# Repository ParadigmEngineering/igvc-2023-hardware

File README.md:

# igvc-2023-hardware
Intelligent Ground Vehicle Competition (Spring 2023) hardware for the Paradigm Engineering Student Group

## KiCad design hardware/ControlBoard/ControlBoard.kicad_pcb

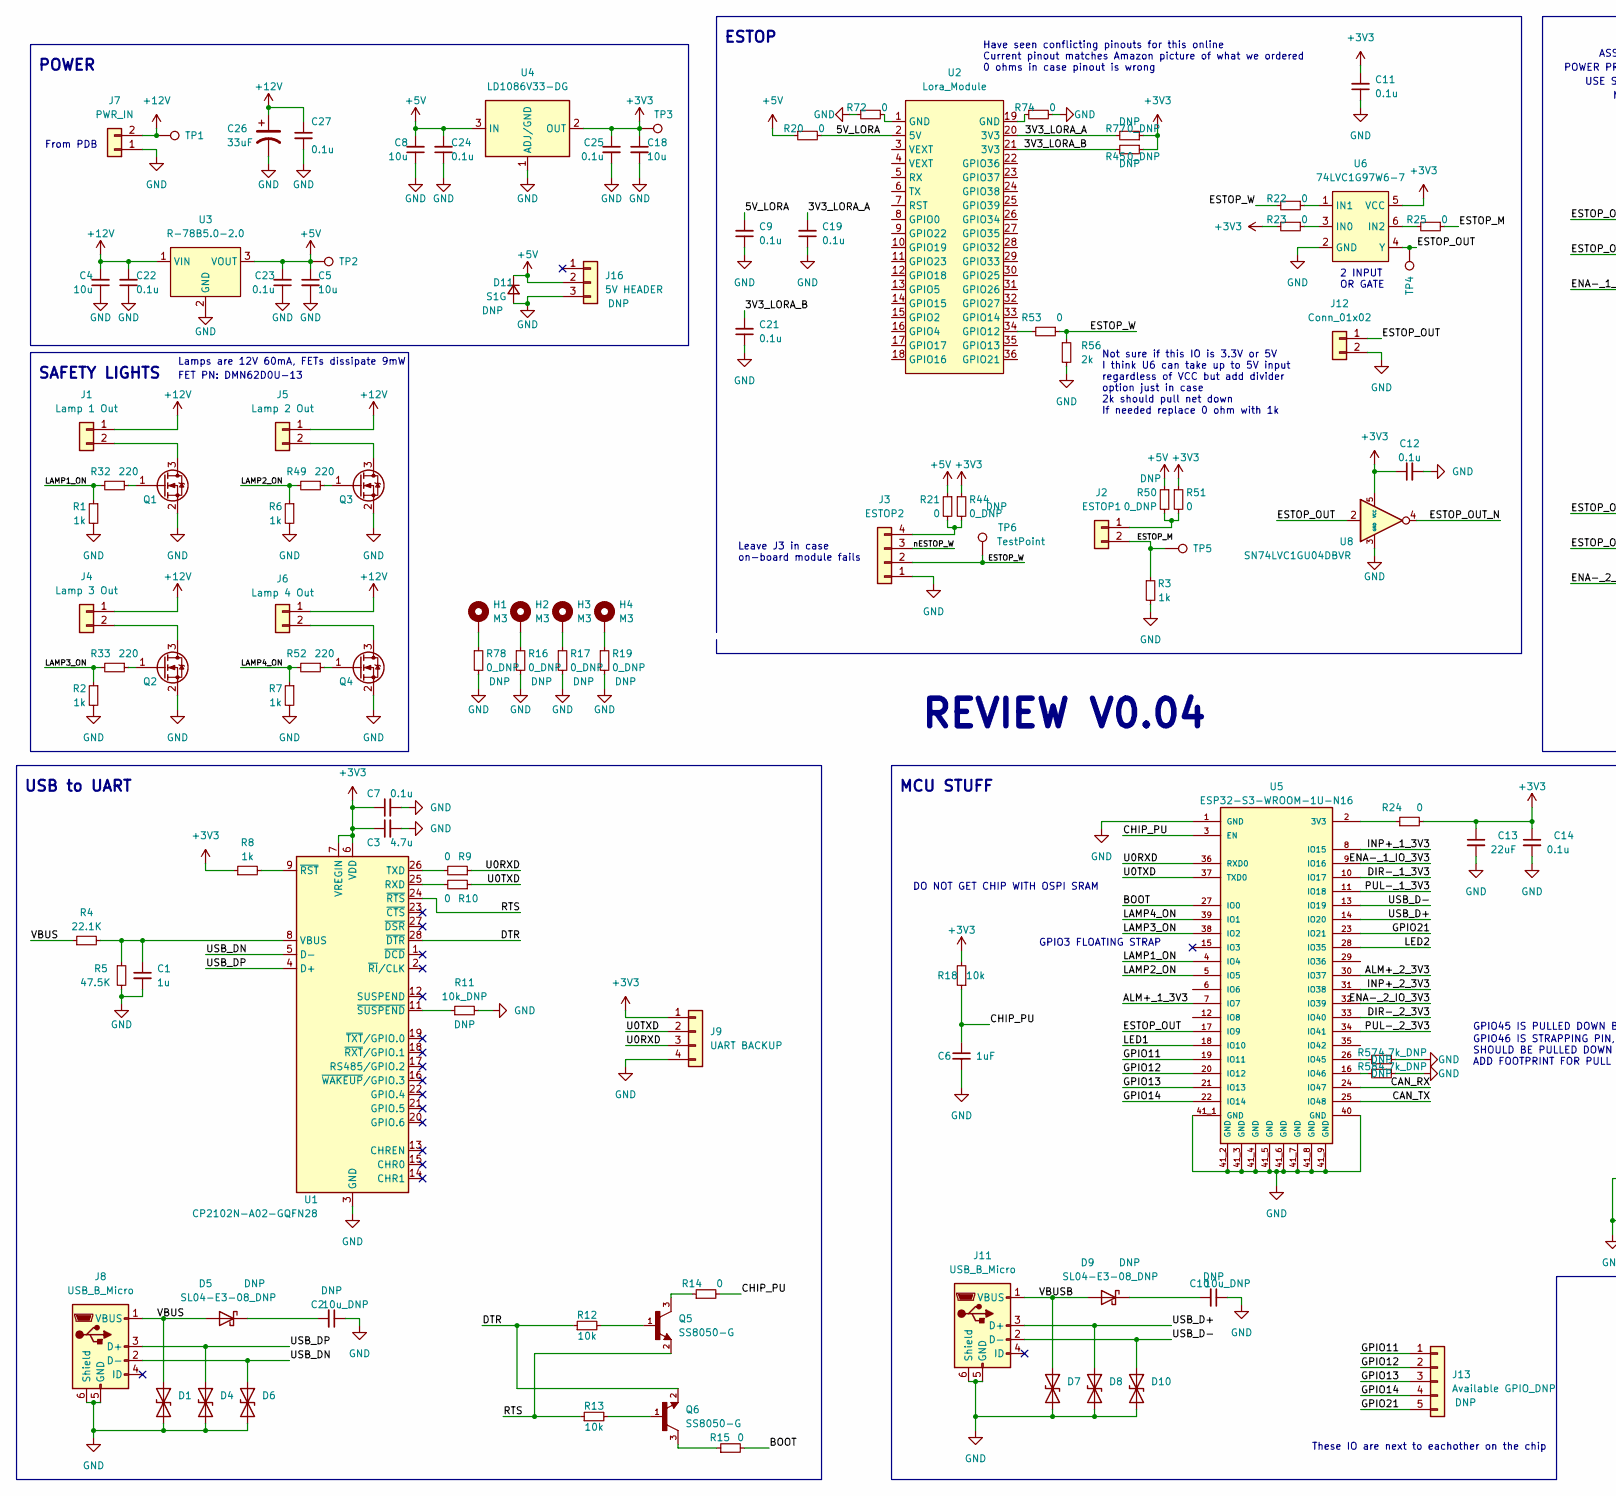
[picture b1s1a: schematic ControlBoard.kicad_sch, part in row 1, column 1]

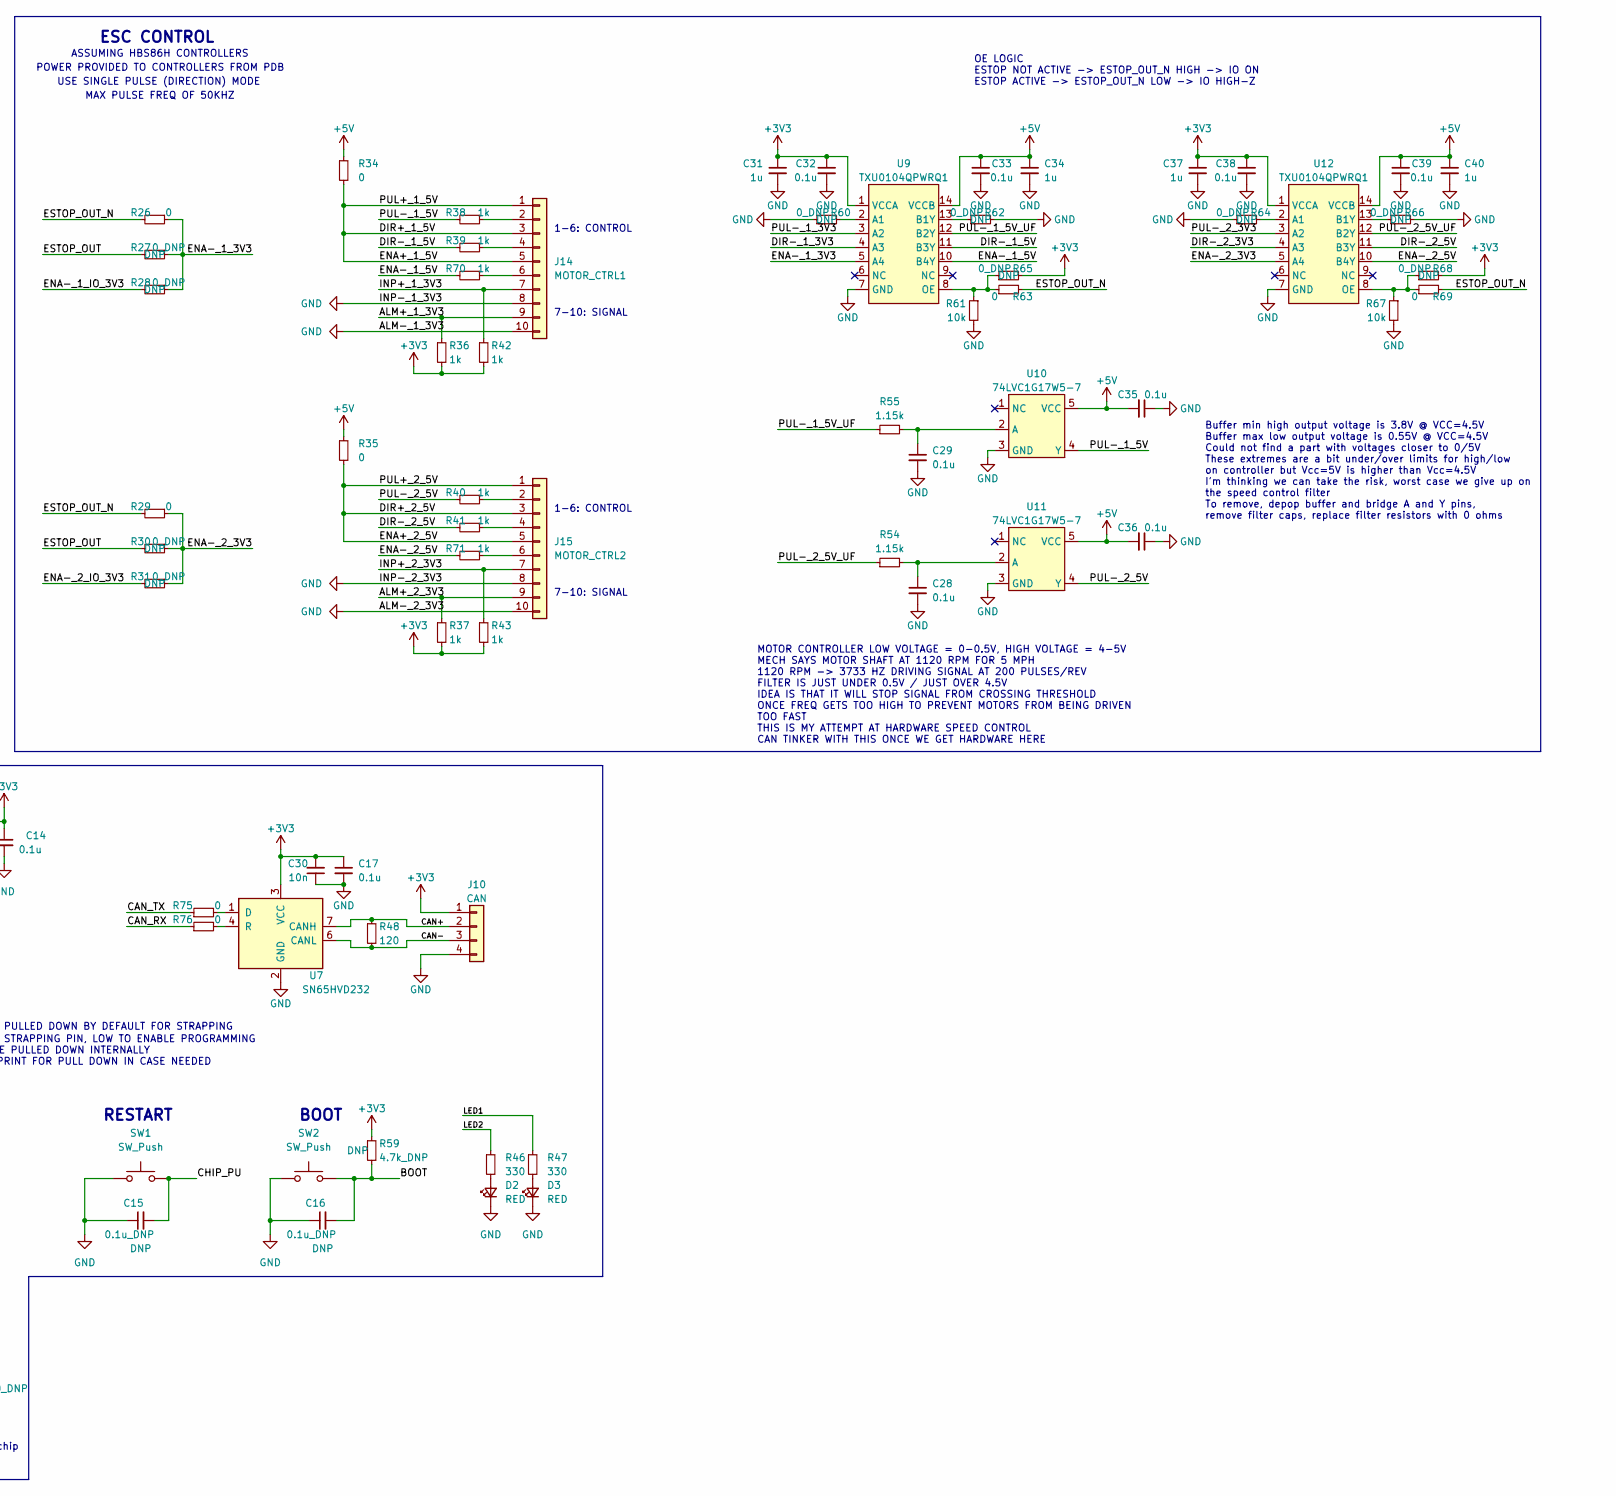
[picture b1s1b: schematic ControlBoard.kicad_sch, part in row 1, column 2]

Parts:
C1: 1u; C_0805_2012Metric; LCSC C116352
C2, C10: 10u_DNP; C_0805_2012Metric; Voltage 5V
C3: 4.7u; C_0805_2012Metric; LCSC C87998
C4: 10u; C_0805_2012Metric; Voltage 12V; LCSC C237493
C5, C8: 10u; C_0805_2012Metric; Voltage 5V; LCSC C237493
C6: 1uF; C_0805_2012Metric; Rating 16V; Voltage 3.3V; LCSC C116352
C7, C9, C12, C19, C21: 0.1u; C_0805_2012Metric; LCSC C519981
C11, C17, C25, C32, C38: 0.1u; C_0805_2012Metric; Voltage 3.3V; LCSC C519981
C13: 22uF; C_0805_2012Metric; Rating 25V; LCSC C128856
C14: 0.1u; C_0805_2012Metric; Rating 25V; LCSC C519981
C15, C16: 0.1u_DNP; C_0805_2012Metric; Voltage 3.3V
C18: 10u; C_0805_2012Metric; Voltage 3.3V; LCSC C237493
C22, C27: 0.1u; C_0805_2012Metric; Voltage 12V; LCSC C519981
C23, C24, C28, C29, C33, C35, C36, C39: 0.1u; C_0805_2012Metric; Voltage 5V; LCSC C519981
C26: 33uF; CP_Radial_D8.0mm_P3.50mm; Digikey 1189-2152-ND
C30: 10n; C_0805_2012Metric; Voltage 3.3V; LCSC C2688117
C31, C37: 1u; C_0805_2012Metric; Voltage 3.3V; LCSC C116352
C34, C40: 1u; C_0805_2012Metric; Voltage 5V; LCSC C116352
D1, D4, D6, D7, D8, D10: SMAJ5.0CA; D_SMA; Digikey SMAJ5.0CALFCT-ND
D2, D3: RED; LED_0603_1608Metric; Digikey 160-1445-1-ND
D5, D9: SL04-E3-08_DNP; D_SMF; Digikey SL04-E3-08GICT-ND
D11: S1G; D_SMA; Digikey 1655-S1GCT-ND
H1, H2, H3, H4: M3; MountingHole_3.2mm_M3_Pad_Via
J1: Lamp 1 Out; Molex_Micro-Fit_3.0_43650-0200_1x02_P3.00mm_Horizontal; Digikey WM1860-ND
J2: ESTOP1; Molex_Micro-Fit_3.0_43650-0200_1x02_P3.00mm_Horizontal; Digikey WM1860-ND
J3: ESTOP2; JST_PH_B4B-PH-K_1x04_P2.00mm_Vertical; LCSC C566011
J4: Lamp 3 Out; Molex_Micro-Fit_3.0_43650-0200_1x02_P3.00mm_Horizontal; Digikey WM1860-ND
J5: Lamp 2 Out; Molex_Micro-Fit_3.0_43650-0200_1x02_P3.00mm_Horizontal; Digikey WM1860-ND
J6: Lamp 4 Out; Molex_Micro-Fit_3.0_43650-0200_1x02_P3.00mm_Horizontal; Digikey WM1860-ND
J7: PWR_IN; Molex_Micro-Fit_3.0_43650-0200_1x02_P3.00mm_Horizontal; Digikey WM1860-ND
J8, J11: USB_B_Micro; USB_Micro-B_Amphenol_10118194_Horizontal; Digikey 609-4618-1-ND
J9: UART BACKUP; PinHeader_1x04_P2.54mm_Vertical; Digikey 664-G800W304018EU-ND
J10: CAN; JST_PH_B4B-PH-K_1x04_P2.00mm_Vertical; LCSC C566011
J12: Conn_01x02; Molex_Micro-Fit_3.0_43650-0200_1x02_P3.00mm_Horizontal; Digikey WM1860-ND
J13: Available GPIO_DNP; PinHeader_1x05_P1.27mm_Vertical; Digikey 2057-HPH1-A-05-UA-ND
J14: MOTOR_CTRL1; Molex_Micro-Fit_3.0_43650-1000_1x10_P3.00mm_Horizontal; Digikey 23-0436501000-ND
J15: MOTOR_CTRL2; Molex_Micro-Fit_3.0_43650-1000_1x10_P3.00mm_Horizontal; Digikey 23-0436501000-ND
J16: 5V HEADER; Molex_KK-254_AE-6410-03A_1x03_P2.54mm_Vertical; Digikey WM4112-ND
Q1, Q2, Q3, Q4: DMN62D0U-13; Digikey DMN62D0U-13DICT-ND
Q5, Q6: SS8050-G; TRANS_SS8050-G; PARTREV A; Digikey 641-1790-1-ND
R1, R2, R3, R6, R7, R8, R36, R37, R38, R39, R40, R41, R42, R43, R70, R71: 1k; R_0805_2012Metric; LCSC C510097
R4: 22.1K; R_0805_2012Metric; LCSC C273840
R5: 47.5K; R_0805_2012Metric; LCSC C137519
R9, R10, R14, R15, R20, R21, R22, R23, R25, R26, R29, R34, R35, R51, R53, R63, R69, R72, R74, R75, R76: 0; R_0805_2012Metric; LCSC C237773
R11: 10k_DNP; R_0805_2012Metric
R12, R13, R18, R61, R67: 10k; R_0805_2012Metric; LCSC C110775
R16, R17, R19, R78: 0_DNP; R_0805_2012Metric
R24: 0; R_0805_2012Metric; LCSC C96345
R27, R28, R30, R31, R44, R45, R50, R60, R62, R64, R65, R66, R68, R77: 0_DNP; R_0805_2012Metric; LCSC C237773
R32, R33, R49, R52: 220; R_0805_2012Metric; LCSC C114519
R46, R47: 330; R_0805_2012Metric; LCSC C105878
R48: 120; R_0805_2012Metric; Digikey 311-120CRCT-ND
R54, R55: 1.15k; R_0805_2012Metric; LCSC C309566
R56: 2k; R_0805_2012Metric; LCSC C127985
R57, R58, R59: 4.7k_DNP; R_0805_2012Metric
SW1, SW2: SW_Push; SW_SPST_B3U-1100P-B; Digikey SW1104CT-ND
TP1, TP2, TP3, TP4, TP5, TP6: TestPoint; TestPoint_Pad_D1.0mm
U1: CP2102N-A02-GQFN28; QFN-28-1EP_5x5mm_P0.5mm_EP3.35x3.35mm; LCSC C964632
U2: Lora_Module
U3: R-78B5.0-2.0; Digikey 945-3042-ND
U4: LD1086V33-DG; TO-220-3_Vertical; Digikey 497-17820-ND
U5: ESP32-S3-WROOM-1U-N16; XCVR_ESP32-S3-WROOM-1U; PARTREV v0.6; LCSC C2980298
U6: 74LVC1G97W6-7; Digikey 74LVC1G97W6-7CT-ND
U7: SN65HVD232; SOIC-8_3.9x4.9mm_P1.27mm; LCSC C30530
U8: SN74LVC1GU04DBVR; SOT-23-5; LCSC C81934
U9, U12: TXU0104QPWRQ1; Digikey 296-TXU0104QPWRQ1CT-ND
U10, U11: 74LVC1G17W5-7; Digikey 74LVC1G17W5-7CT-ND

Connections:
+3V3: C3.1, C7.1, C11.2, C12.1, C13.1, C14.1, C17.1, C18.1, C25.1, C30.2, C31.1, C32.1, C37.1, C38.1, J9.1, J10.1, R8.1, R18.2, R23.2, R24.2, R36.2, R37.2, R42.2, R43.2, R44.1, R45.1, R51.1, R59.1, R65.2, R68.2, R77.1, TP3.1, U1.6 (VDD), U1.7 (VREGIN), U4.2 (OUT), U6.5 (VCC), U7.3 (VCC), U8.5 (VCC), U9.1 (VCCA), U12.1 (VCCA)
+5V: C5.1, C8.2, C23.2, C24.2, C33.1, C34.1, C35.2, C36.2, C39.1, C40.1, D11.1 (K), J16.2, R20.1, R21.1, R34.1, R35.1, R50.1, TP2.1, U3.3 (VOUT), U4.3 (IN), U9.14 (VCCB), U10.5 (VCC), U11.5 (VCC), U12.14 (VCCB)
+12V: C4.2, C22.2, C26.1, C27.1, J1.1, J4.1, J5.1, J6.1, J7.2, TP1.1, U3.1 (VIN)
/3V3_LORA_A: C19.2, R77.2, U2.20 (3V3)
/3V3_LORA_B: C21.2, R45.2, U2.21 (3V3)
/5V_LORA: C9.2, R20.2, U2.2 (5V)
/ALM+_1_3V3: J14.9, R36.1, U5.7 (IO7)
/ALM+_2_3V3: J15.9, R37.1, U5.30 (IO37)
/BOOT: C16.2, R15.2, R59.2, SW2.2, U5.27 (IO0)
/CAN+: J10.2, R48.1, U7.7 (CANH)
/CAN-: J10.3, R48.2, U7.6 (CANL)
/CAN_RX: R76.1, U5.24 (IO47)
/CAN_TX: R75.1, U5.25 (IO48)
/CHIP_PU: C6.1, C15.2, R14.2, R18.1, SW1.2, U5.3 (EN)
/DIR+_1_5V: J14.1, J14.3, J14.5, R34.2
/DIR+_2_5V: J15.1, J15.3, J15.5, R35.2
/DIR-_1_3V3: U5.10 (IO17), U9.4 (A3)
/DIR-_1_5V: R39.2, U9.11 (B3Y)
/DIR-_2_3V3: U5.33 (IO40), U12.4 (A3)
/DIR-_2_5V: R41.2, U12.11 (B3Y)
/DTR: Q6.2, R12.1, U1.28 (~DTR)
/ENA-_1_3V3: R26.1, R27.1, R28.1, U9.5 (A4)
/ENA-_1_5V: R70.2, U9.10 (B4Y)
/ENA-_1_IO_3V3: R28.2, U5.9 (IO16)
/ENA-_2_3V3: R29.1, R30.1, R31.1, U12.5 (A4)
/ENA-_2_5V: R71.2, U12.10 (B4Y)
/ENA-_2_IO_3V3: R31.2, U5.32 (IO39)
/ESTOP_M: J2.2, R3.1, R25.1, TP5.1
/ESTOP_OUT: J12.1, R27.2, R30.2, TP4.1, U5.17 (IO9), U6.4 (Y), U8.2
/ESTOP_OUT_N: R26.2, R29.2, R63.2, R69.2, U8.4
/ESTOP_W: J3.2, R22.2, R53.1, R56.1, TP6.1
/GPIO11: J13.1, U5.19 (IO11)
/GPIO12: J13.2, U5.20 (IO12)
/GPIO13: J13.3, U5.21 (IO13)
/GPIO14: J13.4, U5.22 (IO14)
/GPIO21: J13.5, U5.23 (IO21)
/INP+_1_3V3: J14.7, R42.1, U5.8 (IO15)
/INP+_2_3V3: J15.7, R43.1, U5.31 (IO38)
/LAMP1_ON: R1.1, R32.2, U5.4 (IO4)
/LAMP2_ON: R6.1, R49.2, U5.5 (IO5)
/LAMP3_ON: R2.1, R33.2, U5.38 (IO2)
/LAMP4_ON: R7.1, R52.2, U5.39 (IO1)
/LED1: R47.1, U5.18 (IO10)
/LED2: R46.1, U5.28 (IO35)
/PUL-_1_3V3: U5.11 (IO18), U9.3 (A2)
/PUL-_1_5V: R38.2, U10.4 (Y)
/PUL-_1_5V_UF: R55.1, U9.12 (B2Y)
/PUL-_2_3V3: U5.34 (IO41), U12.3 (A2)
/PUL-_2_5V: R40.2, U11.4 (Y)
/PUL-_2_5V_UF: R54.1, U12.12 (B2Y)
/RTS: Q5.2, R13.1, U1.24 (~RTS)
/U0RXD: J9.3, R9.1, U5.36 (RXD0)
/U0TXD: J9.2, R10.1, U5.37 (TXD0)
/USB_D+: D8.1 (A1), J11.3 (D+), U5.14 (IO20)
/USB_D-: D10.1 (A1), J11.2 (D-), U5.13 (IO19)
/USB_DN: D6.1 (A1), J8.2 (D-), U1.5 (D-)
/USB_DP: D4.1 (A1), J8.3 (D+), U1.4 (D+)
/VBUS: D1.1 (A1), D5.2 (A), J8.1 (VBUS), R4.1
/VBUSB: D7.1 (A1), D9.2 (A), J11.1 (VBUS)
/nESTOP_W: J3.3
GND: C1.2, C2.1, C3.2, C4.1, C5.2, C6.2, C7.2, C8.1, C9.1, C10.1, C11.1, C12.2, C13.2, C14.2, C15.1, C16.1, C17.2, C18.2, C19.1, C21.1, C22.1, C23.1, C24.1, C25.2, C26.2, C27.2, C28.2, C29.2, C30.1, C31.2, C32.2, C33.2, C34.2, C35.1, C36.1, C37.2, C38.2, C39.2, C40.2, D1.2 (A2), D2.1 (K), D3.1 (K), D4.2 (A2), D6.2 (A2), D7.2 (A2), D8.2 (A2), D10.2 (A2), D11.2 (A), J3.1, J7.1, J8.5 (GND), J8.6 (Shield), J9.4, J10.4, J11.5 (GND), J11.6 (Shield), J12.2, J14.8, J14.10, J15.8, J15.10, J16.3, Q1.2 (S), Q2.2 (S), Q3.2 (S), Q4.2 (S), R1.2, R2.2, R3.2, R5.2, R6.2, R7.2, R11.2, R16.2, R17.2, R19.2, R56.2, R57.1, R58.1, R60.1, R61.2, R62.2, R64.1, R66.2, R67.2, R72.1, R74.2, R78.2, SW1.1, SW2.1, U1.3 (GND), U1.29 (GND), U3.2 (GND), U4.1 (ADJ/GND), U5.1 (GND), U5.40 (GND), U5.41_1 (GND), U5.41_2 (GND), U5.41_3 (GND), U5.41_4 (GND), U5.41_5 (GND), U5.41_6 (GND), U5.41_7 (GND), U5.41_8 (GND), U5.41_9 (GND), U6.2 (GND), U7.2 (GND), U8.3 (GND), U9.7 (GND), U10.3 (GND), U11.3 (GND), U12.7 (GND)
unnamed: C1.1, R4.2, R5.1, U1.8 (VBUS)
unnamed: C2.2, D5.1 (K)
unnamed: C10.2, D9.1 (K)
unnamed: C28.1, R54.2, U11.2 (A)
unnamed: C29.1, R55.2, U10.2 (A)
unnamed: D2.2 (A), R46.2
unnamed: D3.2 (A), R47.2
unnamed: H1.1, R78.1
unnamed: H2.1, R16.1
unnamed: H3.1, R17.1
unnamed: H4.1, R19.1
unnamed: J1.2, Q1.3 (D)
unnamed: J2.1, R50.2, R51.2
unnamed: J3.4, R21.2, R44.2
unnamed: J4.2, Q2.3 (D)
unnamed: J5.2, Q3.3 (D)
unnamed: J6.2, Q4.3 (D)
unnamed: J14.2, R38.1
unnamed: J14.4, R39.1
unnamed: J14.6, R70.1
unnamed: J15.2, R40.1
unnamed: J15.4, R41.1
unnamed: J15.6, R71.1
unnamed: Q1.1 (G), R32.1
unnamed: Q2.1 (G), R33.1
unnamed: Q3.1 (G), R49.1
unnamed: Q4.1 (G), R52.1
unnamed: Q5.1, R12.2
unnamed: Q5.3, R14.1
unnamed: Q6.1, R13.2
unnamed: Q6.3, R15.1
unnamed: R8.2, U1.9 (~RST)
unnamed: R9.2, U1.26 (TXD)
unnamed: R10.2, U1.25 (RXD)
unnamed: R11.1, U1.11 (~SUSPEND)
unnamed: R22.1, U6.1 (IN1)
unnamed: R23.1, U6.3 (IN0)
unnamed: R24.1, U5.2 (3V3)
unnamed: R25.2, U6.6 (IN2)
unnamed: R53.2, U2.34 (GPIO12)
unnamed: R57.2, U5.26 (IO45)
unnamed: R58.2, U5.16 (IO46)
unnamed: R60.2, U9.2 (A1)
unnamed: R61.1, R63.1, R65.1, U9.8 (OE)
unnamed: R62.1, U9.13 (B1Y)
unnamed: R64.2, U12.2 (A1)
unnamed: R66.1, U12.13 (B1Y)
unnamed: R67.1, R68.1, R69.1, U12.8 (OE)
unnamed: R72.2, U2.1 (GND)
unnamed: R74.1, U2.19 (GND)
unnamed: R75.2, U7.1 (D)
unnamed: R76.2, U7.4 (R)

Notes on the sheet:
2 INPUT OR GATE
These IO are next to eachother on the chip
Not sure if this IO is 3.3V or 5V I think U6 can take up to 5V input regardless of VCC but add divider option just in case 2k should pull net down If needed replace 0 ohm with 1k
FET PN: DMN62D0U-13
Have seen conflicting pinouts for this online Current pinout matches Amazon picture of what we ordered 0 ohms in case pinout is wrong
POWER
ASSUMING HBS86H CONTROLLERS
MCU STUFF
SAFETY LIGHTS
Buffer min high output voltage is 3.8V @ VCC=4.5V Buffer max low output voltage is 0.55V @ VCC=4.5V Could not find a part with voltages closer to 0/5V These extremes are a bit under/over limits for high/low on controller but Vcc=5V is higher than Vcc=4.5V I'm thinking we can take the risk, worst ca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
1-6: CONTROL
POWER PROVIDED TO CONTROLLERS FROM PDB
ESC CONTROL
GPIO3 FLOATING STRAP
MOTOR CONTROLLER LOW VOLTAGE = 0-0.5V, HIGH VOLTAGE = 4-5V MECH SAYS MOTOR SHAFT AT 1120 RPM FOR 5 MPH 1120 RPM -> 3733 HZ DRIVING SIGNAL AT 200 PULSES/REV FILTER IS JUST UNDER 0.5V / JUST OVER 4.5V IDEA IS THAT IT WILL STOP SIGNAL FROM CROSSING THRESHOLD ONCE FREQ GETS TOO HIGH TO PREVENT MOTORS F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
REVIEW V0.04
USB to UART
From PDB
7-10: SIGNAL
Leave J3 in case on-board module fails
USE SINGLE PULSE (DIRECTION) MODE
GPIO46 IS STRAPPING PIN, LOW TO ENABLE PROGRAMMING SHOULD BE PULLED DOWN INTERNALLY ADD FOOTPRINT FOR PULL DOWN IN CASE NEEDED
DO NOT GET CHIP WITH OSPI SRAM
RESTART
ESTOP
BOOT
Lamps are 12V 60mA, FETs dissipate 9mW
GPIO45 IS PULLED DOWN BY DEFAULT FOR STRAPPING
MAX PULSE FREQ OF 50KHZ
OE LOGIC ESTOP NOT ACTIVE -> ESTOP_OUT_N HIGH -> IO ON ESTOP ACTIVE -> ESTOP_OUT_N LOW -> IO HIGH-Z

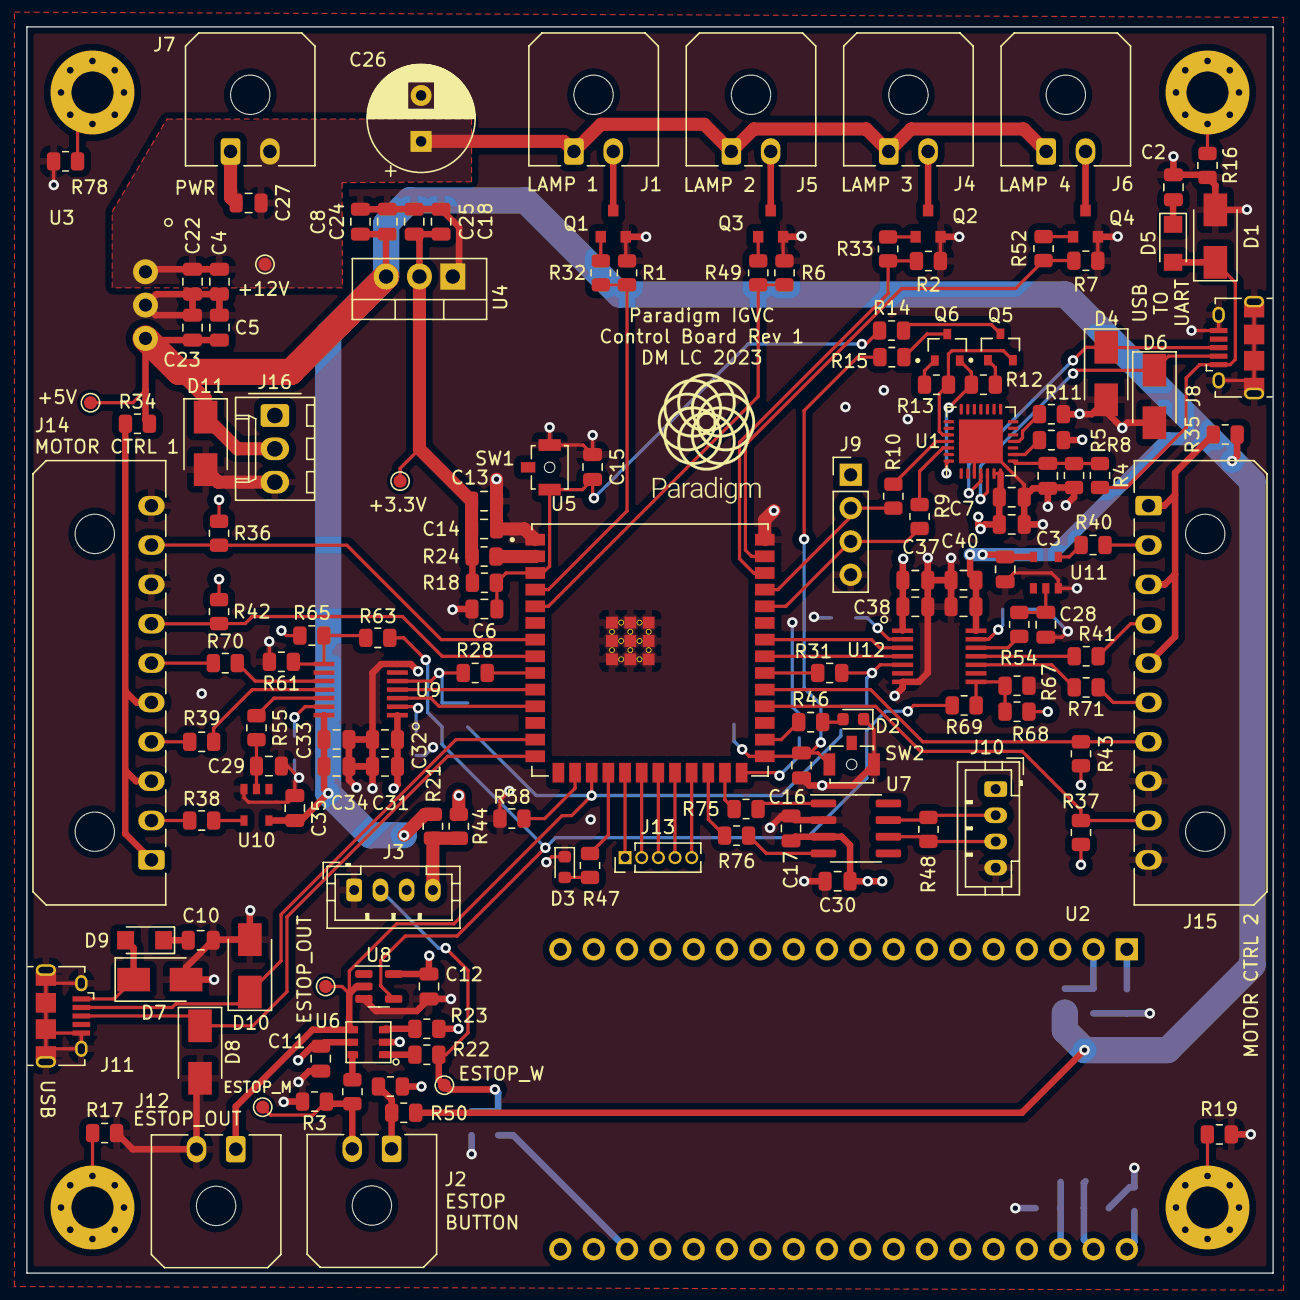
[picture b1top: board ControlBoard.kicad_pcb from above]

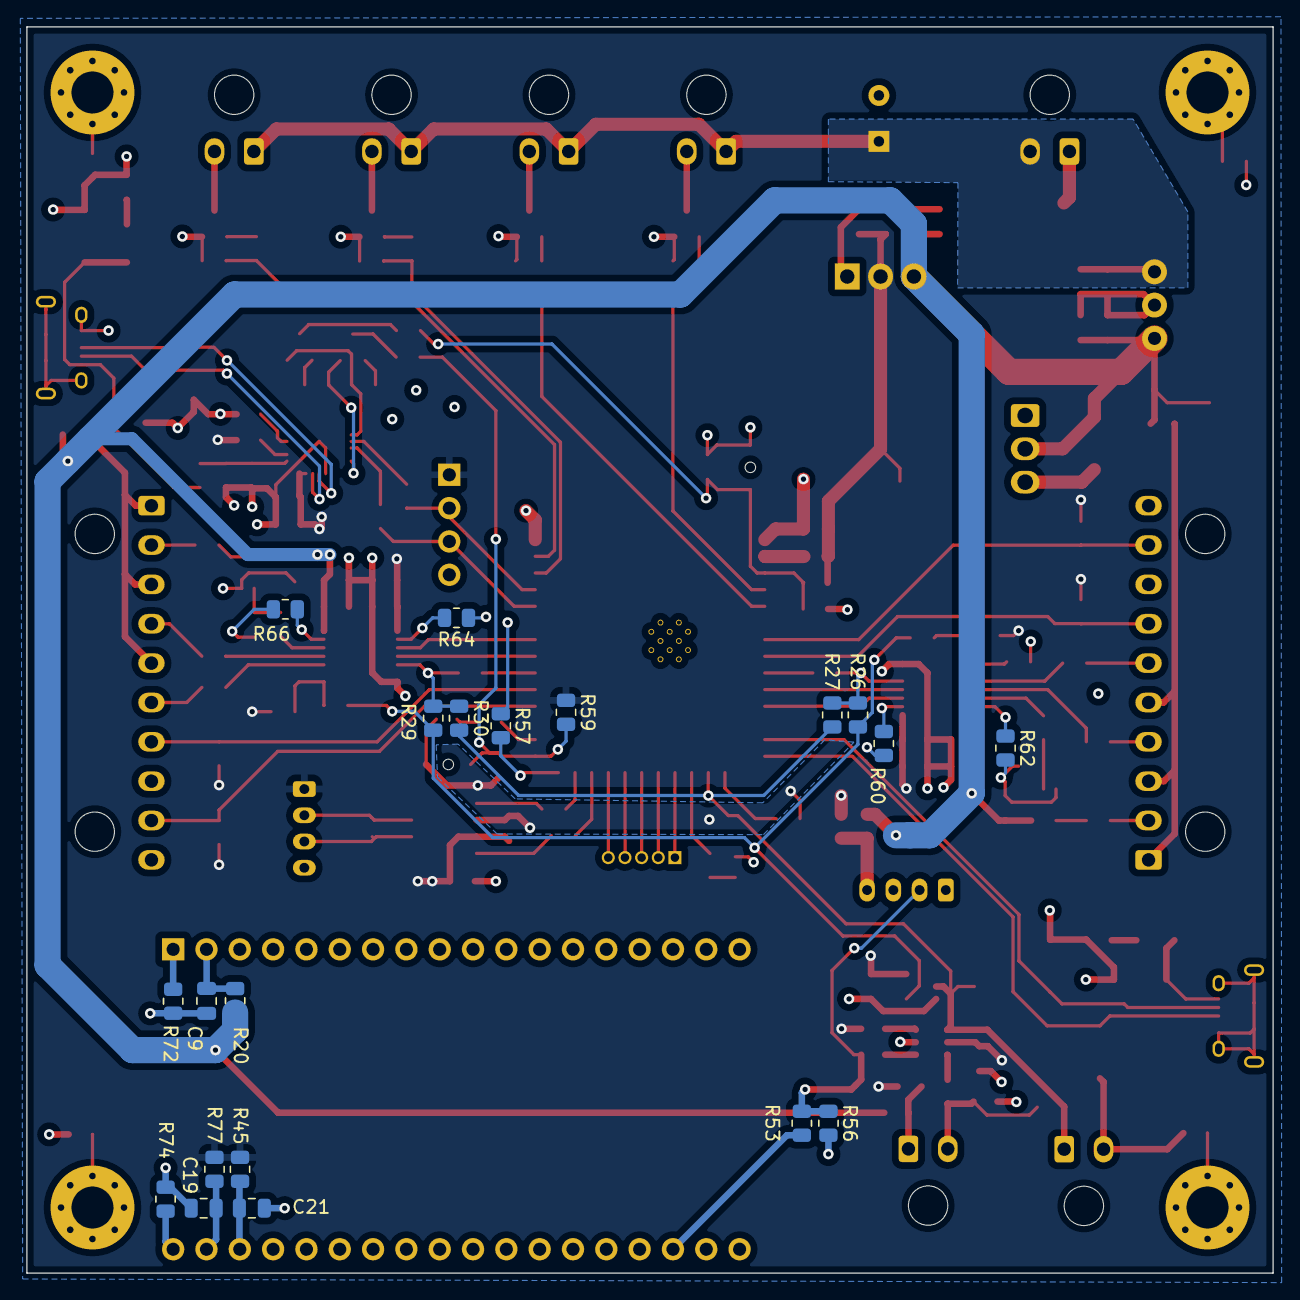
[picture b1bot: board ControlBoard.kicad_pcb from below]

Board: 4 copper layers, 95.0 x 95.0 mm, 173 parts (20 on the bottom side), 112 nets.

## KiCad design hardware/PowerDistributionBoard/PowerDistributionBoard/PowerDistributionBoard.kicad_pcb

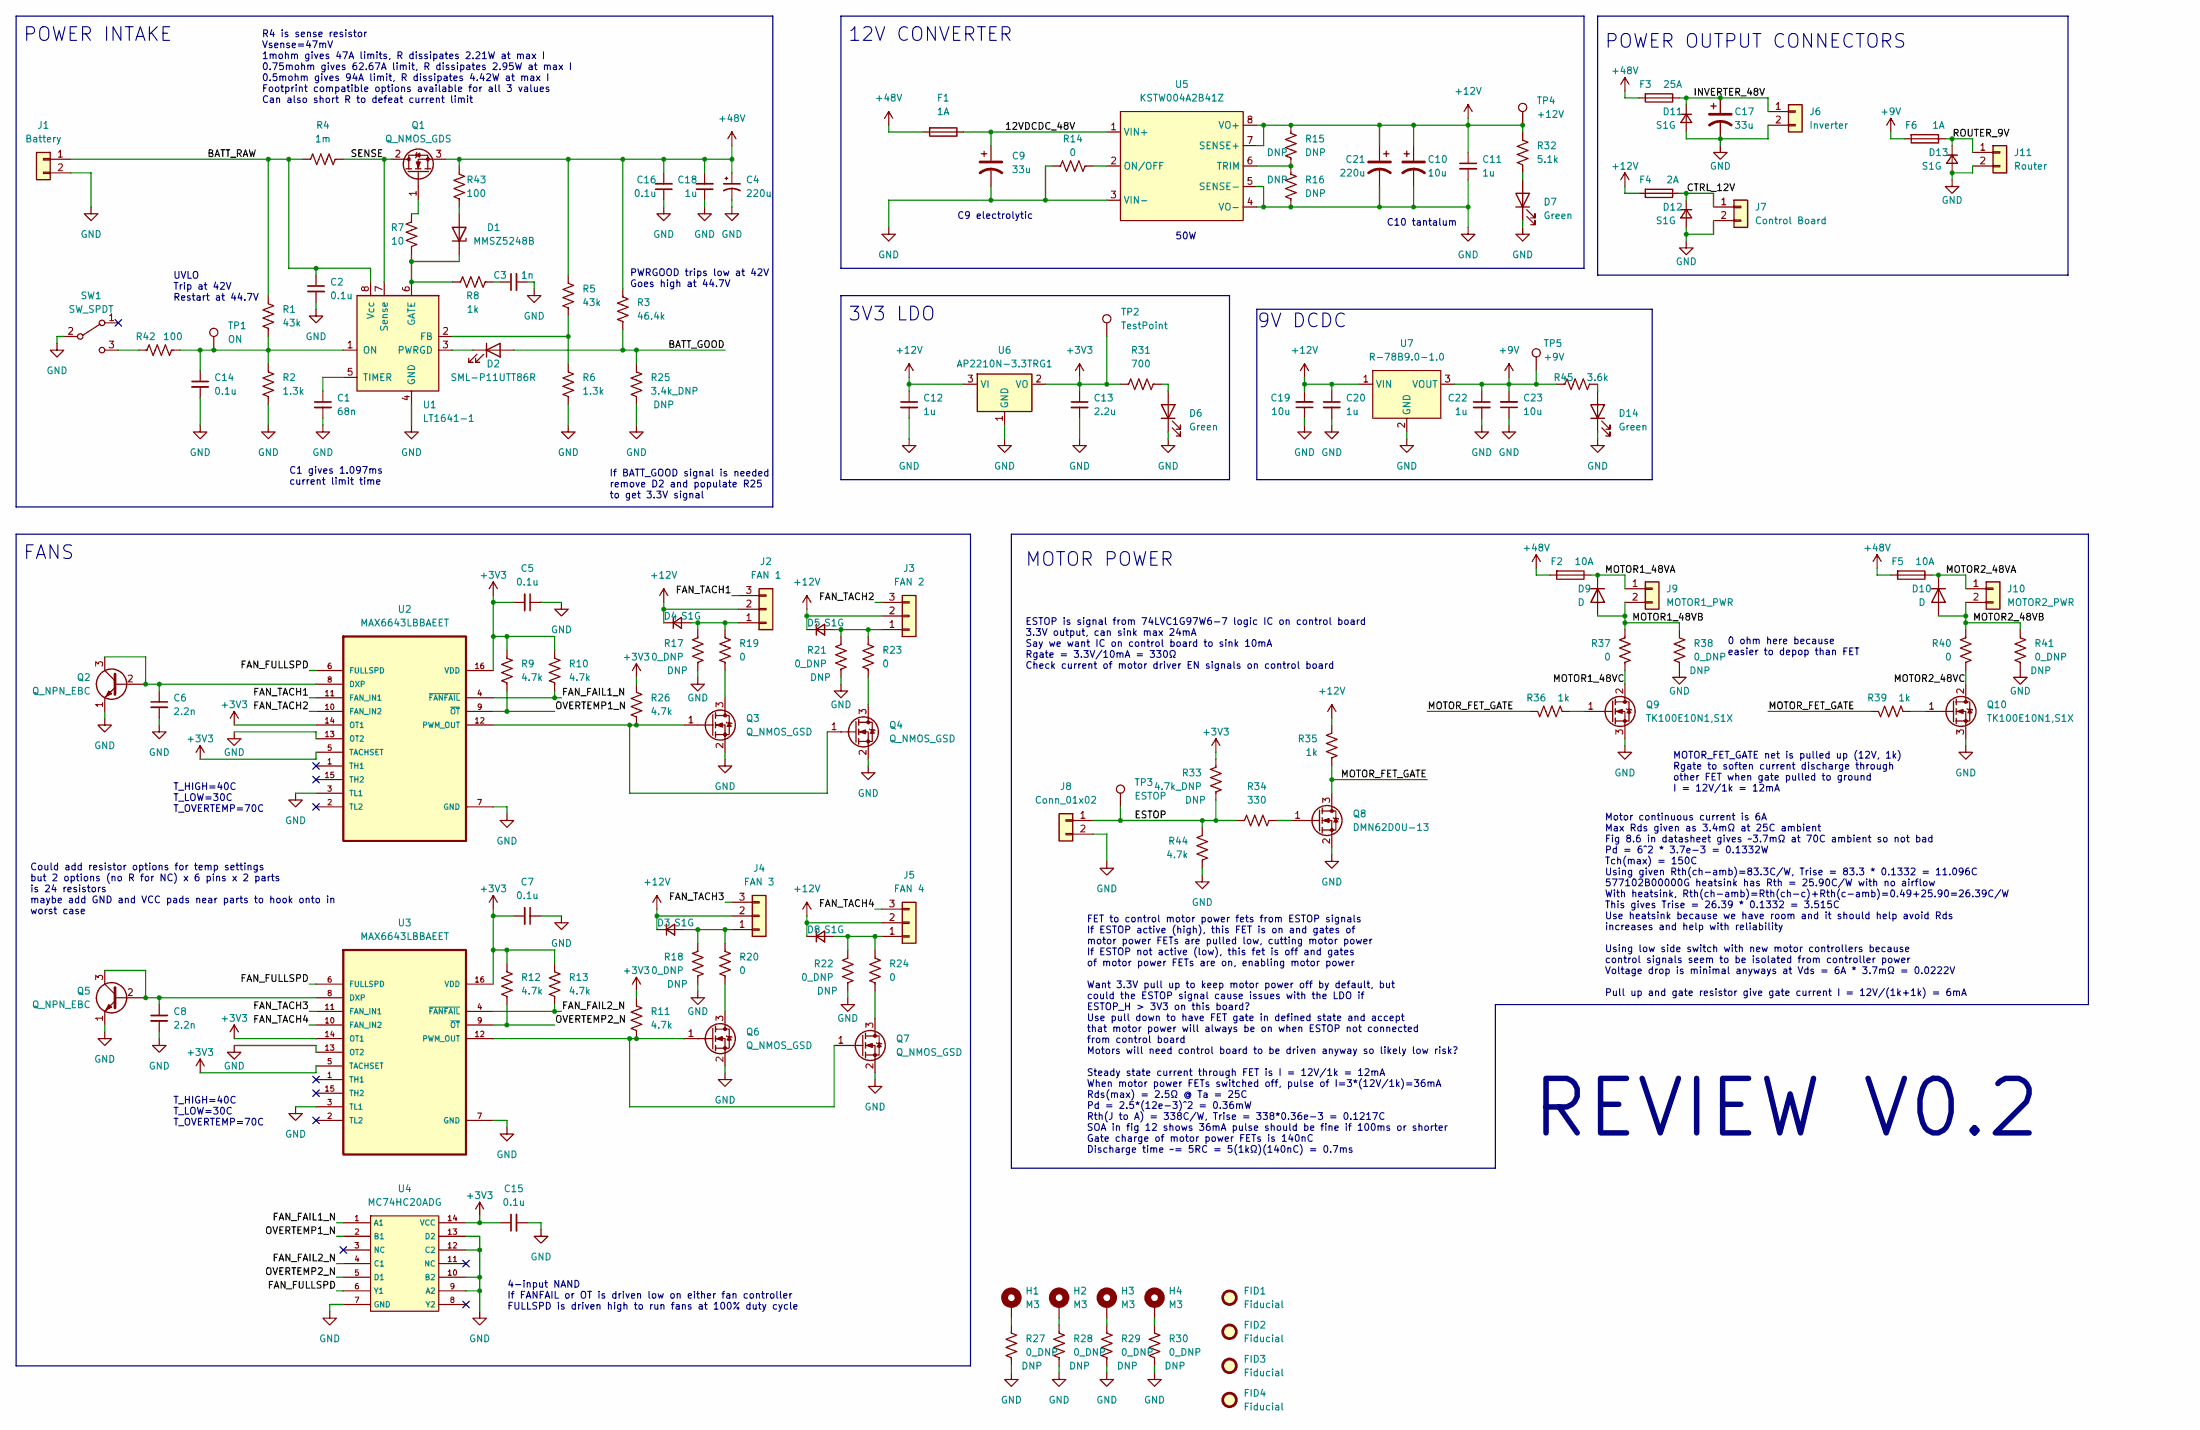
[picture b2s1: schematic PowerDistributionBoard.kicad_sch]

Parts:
C1: 68n; C_0805_2012Metric; Voltage 44V; LCSC C113842
C2, C14, C16: 0.1u; C_0805_2012Metric; Voltage 48V; LCSC C28233
C3: 1n; C_0805_2012Metric; Voltage 68V; LCSC C16005
C4: 220u; CP_Radial_D16.0mm_P7.50mm; Voltage 48V; Digikey 493-5867-ND
C5, C7, C15: 0.1u; C_0805_2012Metric; Voltage 3.3V; LCSC C597440
C6, C8: 2.2n; C_0805_2012Metric; Voltage 0.8V; LCSC C1728
C9, C17: 33u; CP_Radial_D10.0mm_P5.00mm; Digikey 1189-2207-ND
C10: 10u; C_1206_3216Metric; Digikey 478-10001-1-ND
C11, C12, C20: 1u; C_0805_2012Metric; Voltage 12V; LCSC C116352
C13: 2.2u; C_0805_2012Metric; Voltage 3.3V; LCSC C107366
C18: 1u; C_0805_2012Metric; Voltage 48V; LCSC C28233
C19: 10u; C_0805_2012Metric; Voltage 12V; LCSC C237493
C21: 220u; CP_Radial_D6.3mm_P2.50mm; Voltage 12V; Digikey 1189-2913-ND
C22: 1u; C_0805_2012Metric; Voltage 9V; LCSC C116352
C23: 10u; C_0805_2012Metric; Voltage 9V; LCSC C237493
D1: MMSZ5248B; D_SOD-123; Digikey MMSZ5248B-HE3-08GICT-ND
D2: SML-P11UTT86R; LED_0402_1005Metric; Digikey SML-P11UTT86RCT-ND
D3, D4, D5, D8, D11, D12, D13: S1G; D_SMA; Digikey 1655-S1GCT-ND
D6, D7, D14: Green; LED_0805_2012Metric_Pad1.15x1.40mm_HandSolder; Digikey 492-2525-1-ND
D9, D10: D; VS-15AWL06FNTR-M3; Digikey VS-15AWL06FNTR-M3GICT-ND
F1, F6: 1A; 3557-2; Digikey 36-3557-2-ND
F2, F5: 10A; 3557-2; Digikey 36-3557-2-ND
F3: 25A; 3557-2; Digikey 36-3557-2-ND
F4: 2A; 3557-2; Digikey 36-3557-2-ND
FID1, FID2, FID3, FID4: Fiducial; Fiducial_1mm_Mask2mm
H1, H2, H3, H4: M3; MountingHole_3.2mm_M3_Pad_Via
J1: Battery; Molex_Mini-Fit_Sr_42820-22XX_1x02_P10.00mm_Horizontal; Digikey WM11250-ND
J2: FAN 1; Molex_KK-254_AE-6410-03A_1x03_P2.54mm_Vertical; Digikey WM4112-ND
J3: FAN 2; Molex_KK-254_AE-6410-03A_1x03_P2.54mm_Vertical; Digikey WM4112-ND
J4: FAN 3; Molex_KK-254_AE-6410-03A_1x03_P2.54mm_Vertical; Digikey WM4112-ND
J5: FAN 4; Molex_KK-254_AE-6410-03A_1x03_P2.54mm_Vertical; Digikey WM4112-ND
J6: Inverter; Molex_Mini-Fit_Sr_42820-22XX_1x02_P10.00mm_Horizontal; Digikey WM11250-ND
J7: Control Board; Molex_Micro-Fit_3.0_43650-0215_1x02_P3.00mm_Vertical; Digikey WM1917-ND
J8: Conn_01x02; Molex_Micro-Fit_3.0_43650-0215_1x02_P3.00mm_Vertical; Digikey WM1917-ND
J9: MOTOR1_PWR; Molex_Mini-Fit_Sr_42820-22XX_1x02_P10.00mm_Horizontal; Digikey WM11250-ND
J10: MOTOR2_PWR; Molex_Mini-Fit_Sr_42820-22XX_1x02_P10.00mm_Horizontal; Digikey WM11250-ND
J11: Router; Molex_Micro-Fit_3.0_43650-0215_1x02_P3.00mm_Vertical; Digikey WM1917-ND
Q1: Q_NMOS_GDS; TO-263-2; Digikey 296-49604-1-ND
Q2, Q5: Q_NPN_EBC; SST3904T116CT-ND; Digikey SST3904T116CT-ND
Q3, Q4, Q6, Q7: Q_NMOS_GSD; SC-59; Digikey BSR802NL6327HTSA1CT-ND
Q8: DMN62D0U-13; Digikey DMN62D0U-13DICT-ND
Q9, Q10: TK100E10N1,S1X; TO-220-3_Vertical; Digikey TK100E10N1S1X-ND
R1, R5: 43k; R_0805_2012Metric; LCSC C137524
R2, R6: 1.3k; R_0805_2012Metric; LCSC C137582
R3: 46.4k; R_0805_2012Metric; LCSC C317450
R4: 1m; Y14860R00075F9R; Digikey_0.75m 804-Y14860R00075F9RCT-ND
R7: 10; R_0805_2012Metric; LCSC C2074472
R8, R35, R36, R39: 1k; R_0805_2012Metric; LCSC C510097
R9, R10, R11, R12, R13, R26, R44: 4.7k; R_0805_2012Metric; LCSC C140869
R14, R19, R20, R23, R24: 0; R_0805_2012Metric; LCSC C237773
R15, R16: DNP; R_0805_2012Metric
R17, R18, R21, R22, R27, R28, R29, R30: 0_DNP; R_0805_2012Metric
R25: 3.4k_DNP; R_0805_2012Metric
R31: 700; R_0805_2012Metric; LCSC C483228
R32: 5.1k; R_0805_2012Metric; LCSC C84375
R33: 4.7k_DNP; R_0805_2012Metric
R34: 330; R_0805_2012Metric; LCSC C105878
R37, R40: 0; R_2512_6332Metric; Digikey HCJ2512ZT0R00CT-ND
R38, R41: 0_DNP; R_2512_6332Metric; Digikey HCJ2512ZT0R00CT-ND
R42, R43: 100; R_0805_2012Metric; LCSC C105577
R45: 3.6k; R_0805_2012Metric; LCSC C137533
SW1: SW_SPDT; EG1218; Digikey EG1903-ND
TP1: ON; TestPoint_Pad_D1.0mm
TP2: TestPoint; TestPoint_Pad_D1.0mm
TP3: ESTOP; TestPoint_Pad_D1.0mm
TP4: +12V; TestPoint_Pad_D1.0mm
TP5: +9V; TestPoint_Pad_D1.0mm
U1: LT1641-1; LT1641-1CS8#TRPBF; Digikey LT1641-1CS8#TRPBFCT-ND
U2, U3: MAX6643LBBAEET; QSOP-16_3.9x4.9mm_P0.635mm; Digikey MAX6643LBBAEE+TCT-ND
U4: MC74HC20ADG; SOIC-14_3.9x8.7mm_P1.27mm; Digikey MC74HC20ADGOS-ND
U5: KSTW004A2B41Z; CONV_KSTW004A2B41Z; Digikey 555-1330-ND
U6: AP2210N-3.3TRG1; Digikey AP2210N-3.3TRG1DICT-ND
U7: R-78B9.0-1.0; Digikey 945-1056-ND

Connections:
+3V3: C5.2, C7.2, C13.1, C15.1, R9.1, R10.1, R11.1, R12.1, R13.1, R26.1, R31.2, R33.2, TP2.1, U2.5 (TACHSET), U2.14 (OT1), U2.16 (VDD), U3.5 (TACHSET), U3.14 (OT1), U3.16 (VDD), U4.14 (VCC), U6.2 (VO)
+9V: C22.1, C23.2, F6.2, R45.2, TP5.1, U7.3 (VOUT)
+12V: C10.1, C11.1, C12.1, C19.2, C20.1, C21.1, D3.1 (K), D4.1 (K), D5.1 (K), D8.1 (K), F4.2, J2.2, J3.2, J4.2, J5.2, R15.1, R32.1, R35.2, TP4.1, U5.7 (SENSE+), U5.8 (VO+), U6.3 (VI), U7.1 (VIN)
+48V: C4.1, C16.2, C18.2, F1.2, F2.2, F3.2, F5.2, Q1.3 (S), R3.1, R5.1, R43.2
/12VDCDC_48V: C9.1, F1.1, U5.1 (VIN+)
/BATT_GOOD: D2.2 (A), R3.2, R25.1
/BATT_RAW: C2.1, J1.1, R1.1, R4.2, U1.8 (Vcc)
/CTRL_12V: D12.1 (K), F4.1, J7.1
/ESTOP: J8.1, R33.1, R34.2, R44.2, TP3.1
/FAN_FAIL1_N: R10.2, U2.4 (~FANFAIL), U4.1 (A1)
/FAN_FAIL2_N: R13.2, U3.4 (~FANFAIL), U4.4 (C1)
/FAN_FULLSPD: U2.6 (FULLSPD), U3.6 (FULLSPD), U4.6 (Y1)
/FAN_TACH1: J2.3, U2.11 (FAN_IN1)
/FAN_TACH2: J3.3, U2.10 (FAN_IN2)
/FAN_TACH3: J4.3, U3.11 (FAN_IN1)
/FAN_TACH4: J5.3, U3.10 (FAN_IN2)
/INVERTER_48V: C17.1, D11.1 (K), F3.1, J6.1
/MOTOR1_48VA: D9.1 (K), F2.1, J9.1
/MOTOR1_48VB: D9.2 (A), J9.2, R37.2, R38.1
/MOTOR1_48VC: Q9.2 (D), R37.1
/MOTOR2_48VA: D10.1 (K), F5.1, J10.1
/MOTOR2_48VB: D10.2 (A), J10.2, R40.2, R41.1
/MOTOR2_48VC: Q10.2 (D), R40.1
/MOTOR_FET_GATE: Q8.3 (D), R35.1, R36.1, R39.1
/OVERTEMP1_N: R9.2, U2.9 (~OT), U4.2 (B1)
/OVERTEMP2_N: R12.2, U3.9 (~OT), U4.5 (D1)
/ROUTER_9V: D13.1 (K), F6.1, J11.1
/SENSE: Q1.2 (D), R4.1, U1.7 (Sense)
GND: C1.2, C2.2, C3.2, C4.2, C5.1, C6.2, C7.1, C8.2, C9.2, C10.2, C11.2, C12.2, C13.2, C14.2, C15.2, C16.1, C17.2, C18.1, C19.1, C20.2, C21.2, C22.2, C23.1, D6.1 (K), D7.1 (K), D11.2 (A), D12.2 (A), D13.2 (A), D14.1 (K), J1.2, J6.2, J7.2, J8.2, J11.2, Q2.1 (E), Q3.2 (S), Q4.2 (S), Q5.1 (E), Q6.2 (S), Q7.2 (S), Q8.2 (S), Q9.3 (S), Q10.3 (S), R2.2, R6.2, R14.2, R16.2, R17.1, R18.1, R21.1, R22.1, R25.2, R27.2, R28.2, R29.2, R30.2, R38.2, R41.2, R44.1, SW1.2 (B), U1.4 (GND), U2.3 (TL1), U2.7 (GND), U2.13 (OT2), U3.3 (TL1), U3.7 (GND), U3.13 (OT2), U4.7 (GND), U4.9 (A2), U4.10 (B2), U4.12 (C2), U4.13 (D2), U5.3 (VIN-), U5.4 (VO-), U5.5 (SENSE-), U6.1 (GND), U7.2 (GND)
unnamed: C1.1, U1.5 (TIMER)
unnamed: C3.1, R8.1
unnamed: C6.1, Q2.2 (B), Q2.3 (C), U2.8 (DXP)
unnamed: C8.1, Q5.2 (B), Q5.3 (C), U3.8 (DXP)
unnamed: C14.1, R1.2, R2.1, R42.1, TP1.1, U1.1 (ON)
unnamed: D1.1 (K), R7.1, R8.2, U1.6 (GATE)
unnamed: D1.2 (A), R43.1
unnamed: D2.1 (K), U1.3 (PWRGD)
unnamed: D3.2 (A), J4.1, R18.2, R20.1
unnamed: D4.2 (A), J2.1, R17.2, R19.1
unnamed: D5.2 (A), J3.1, R21.2, R23.1
unnamed: D6.2 (A), R31.1
unnamed: D7.2 (A), R32.2
unnamed: D8.2 (A), J5.1, R22.2, R24.1
unnamed: D14.2 (A), R45.1
unnamed: H1.1, R27.1
unnamed: H2.1, R28.1
unnamed: H3.1, R29.1
unnamed: H4.1, R30.1
unnamed: Q1.1 (G), R7.2
unnamed: Q3.1 (G), Q4.1 (G), R26.2, U2.12 (PWM_OUT)
unnamed: Q3.3 (D), R19.2
unnamed: Q4.3 (D), R23.2
unnamed: Q6.1 (G), Q7.1 (G), R11.2, U3.12 (PWM_OUT)
unnamed: Q6.3 (D), R20.2
unnamed: Q7.3 (D), R24.2
unnamed: Q8.1 (G), R34.1
unnamed: Q9.1 (G), R36.2
unnamed: Q10.1 (G), R39.2
unnamed: R5.2, R6.1, U1.2 (FB)
unnamed: R14.1, U5.2 (ON/OFF)
unnamed: R15.2, R16.1, U5.6 (TRIM)
unnamed: R42.2, SW1.3 (C)

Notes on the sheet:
C9 electrolytic
POWER INTAKE
C1 gives 1.097ms current limit time
POWER OUTPUT CONNECTORS
Motor continuous current is 6A Max Rds given as 3.4mΩ at 25C ambient Fig 8.6 in datasheet gives ~3.7mΩ at 70C ambient so not bad Pd = 6^2 * 3.7e-3 = 0.1332W Tch(max) = 150C Using given Rth(ch-amb)=83.3C/W, Trise = 83.3 * 0.1332 = 11.096C 577102B00000G heatsink has Rth = 25.90C/W with no airflow Wit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
T_HIGH=40C T_LOW=30C T_OVERTEMP=70C
UVLO Trip at 42V Restart at 44.7V
PWRGOOD trips low at 42V Goes high at 44.7V
4-input NAND If FANFAIL or OT is driven low on either fan controller FULLSPD is driven high to run fans at 100% duty cycle
0 ohm here because easier to depop than FET
R4 is sense resistor Vsense=47mV 1mohm gives 47A limits, R dissipates 2.21W at max I 0.75mohm gives 62.67A limit, R dissipates 2.95W at max I 0.5mohm gives 94A limit, R dissipates 4.42W at max I Footprint compatible options available for all 3 values Can also short R to defeat current limit
50W
Could add resistor options for temp settings but 2 options (no R for NC) x 6 pins x 2 parts is 24 resistors maybe add GND and VCC pads near parts to hook onto in worst case
MOTOR_FET_GATE net is pulled up (12V, 1k) Rgate to soften current discharge through other FET when gate pulled to ground I = 12V/1k = 12mA
C10 tantalum
3V3 LDO
If BATT_GOOD signal is needed remove D2 and populate R25 to get 3.3V signal
12V CONVERTER
REVIEW V0.2
FANS
ESTOP is signal from 74LVC1G97W6-7 logic IC on control board 3.3V output, can sink max 24mA Say we want IC on control board to sink 10mA Rgate = 3.3V/10mA = 330Ω Check current of motor driver EN signals on control board
MOTOR POWER
FET to control motor power fets from ESTOP signals If ESTOP active (high), this FET is on and gates of motor power FETs are pulled low, cutting motor power If ESTOP not active (low), this fet is off and gates of motor power FETs are on, enabling motor power Want 3.3V pull up to keep motor power off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
9V DCDC
